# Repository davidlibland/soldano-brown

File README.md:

# Soldano BSIAB
This repo contains schematics and parts lists for a soldano clone based on the Brown Sound in a Box (BSIAB) pedal. It relies on cascading push-pull jfets.

It fits this enclosure: https://www.taydaelectronics.com/hardware/enclosures/matte-white-pedalpcb-125b-bare-drilled-enclosure-type-5-1.html

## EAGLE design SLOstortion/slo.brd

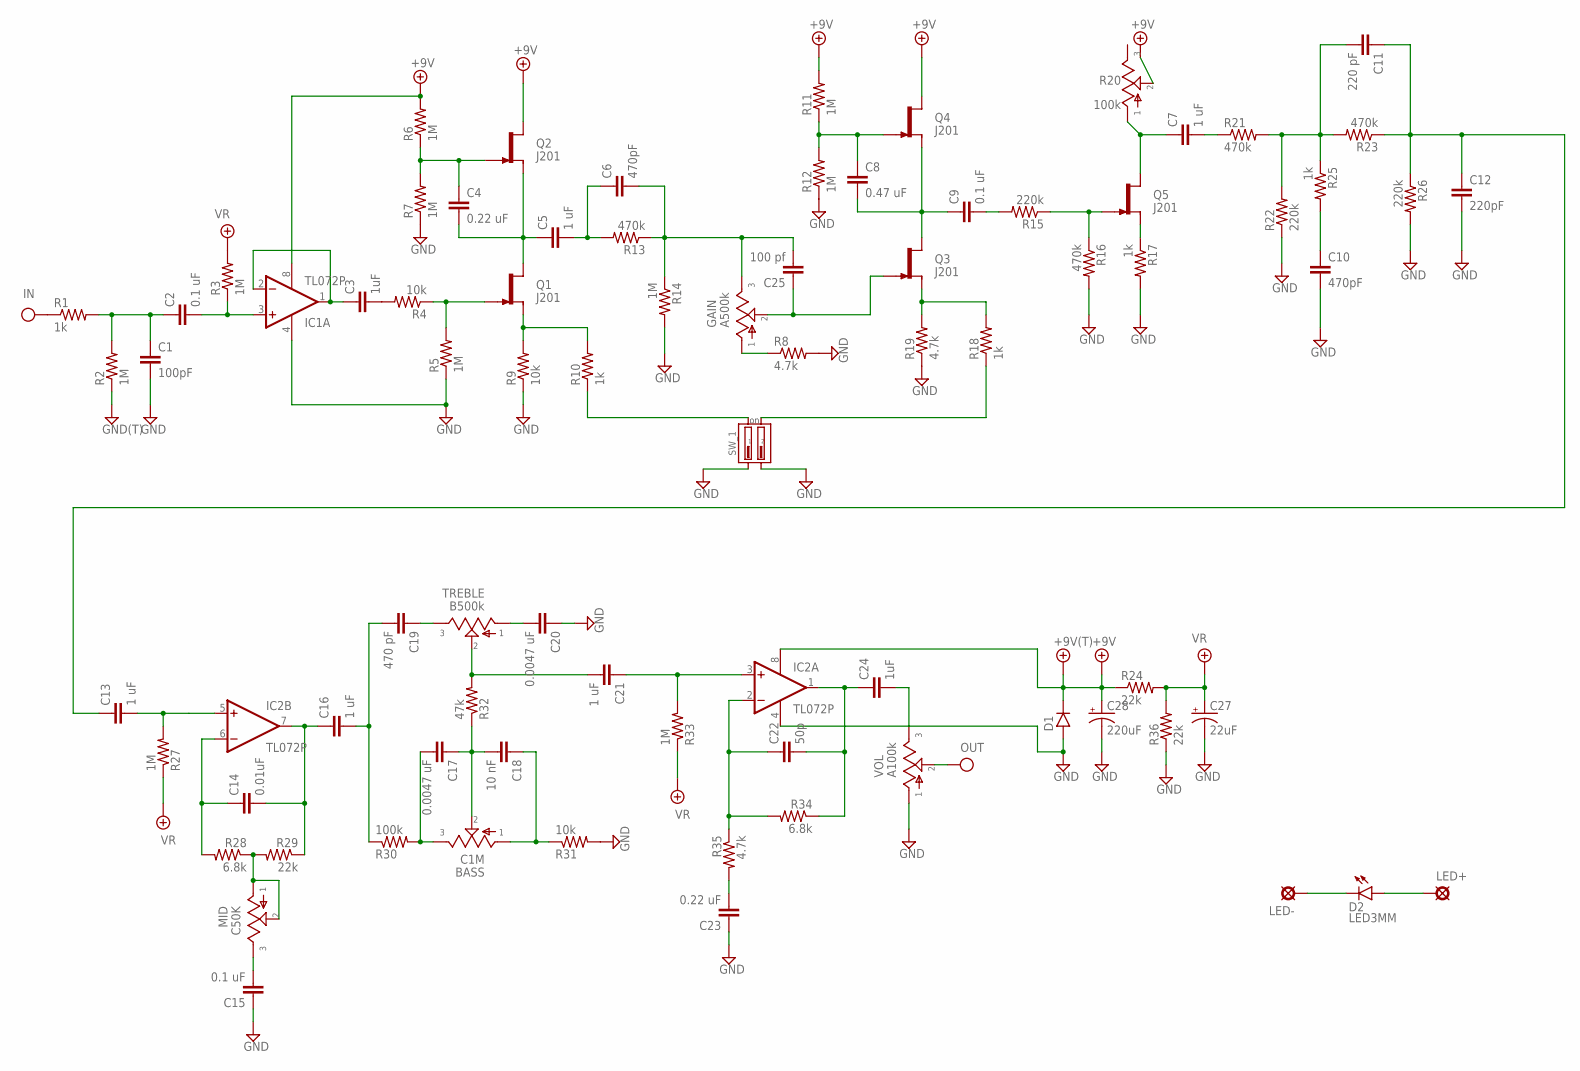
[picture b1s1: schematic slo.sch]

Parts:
+9V: +9V(T); SQUARE
BASS: C1M; 16MM
C1: 100pF; 050X030_050
C2, C9: 0.1 uF; 080X045
C3, C24: 1uF; 080X050
C4, C23: 0.22 uF; 080X045
C5: 1 uF; 070X030
C6: 470pF; 050X030_050
C7, C13, C16, C21: 1 uF; 080X050
C8: 0.47 uF; 080X045
C10: 470pF; 070X030
C11: 220 pF; 075X035_3
C12: 220pF; 075X035_3
C14: 0.01uF; 050X030_050_1
C15: 0.1 uF; 075X040_3
C17, C20: 0.0047 uF; 075X035
C18: 10 nF; 075X035
C19: 470 pF; 075X030
C22: 50p; 050X030_050_1
C25: 100 pf; 050X030_050_1
C27: 22uF; 050_020
C28: 220uF; 063_025
D1: 1N400X.1; DO41-1
D2: LED3MM
GAIN: A500k; 16MM
GND: GND(T); SQUARE
IC1, IC2: TL072P; DIL08
IN: IN(T); SQUARE
LED+: PADO; ROUND
LED-: PAD; SQUARE
MID: C50K; 16MM
OUT: OUT(T); SQUARE
Q1, Q2, Q3, Q4, Q5: J201; TO92-
R1, R10, R17, R18, R25: 1k; R0204/2
R2, R3, R5, R6, R7, R11, R12, R14, R27, R33: 1M; R0204/2
R4, R9, R31: 10k; R0204/2
R8, R19, R35: 4.7k; R0204/2
R13, R16, R21, R23: 470k; R0204/2
R15, R22, R26: 220k; R0204/2
R20: 100k; B25P
R24, R29, R36: 22k; R0204/2
R28, R34: 6.8k; R0204/2
R30: 100k; R0204/2
R32: 47k; R0204/2
SW_1: DIP2; DIP2.B
TREBLE: B500k; 16MM
VOL: A100k; 16MM

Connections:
+9V: +9V.1, C28.+, D1.C, IC1.8 (V+), IC2.8 (V+), Q2.3 (D), Q4.3 (D), R6.2, R11.2, R20.2, R24.1
GND: C1.2, C10.2, C12.2, C15.1, C20.1, C23.1, C27.-, C28.-, D1.A, GND.1, IC1.4 (V-), IC2.4 (V-), R2.1, R5.1, R7.1, R8.2, R9.1, R12.1, R14.2, R16.2, R17.2, R19.1, R22.1, R26.2, R31.2, R36.1, SW_1.P$1 (1), SW_1.P$3 (3), VOL.1
IN: IN.1, R1.1
unnamed: C1.1, C2.1, R1.2, R2.2
unnamed: C2.2, IC1.3 (+IN), R3.1
unnamed: C3.1, IC1.1 (OUT), IC1.2 (-IN)
unnamed: C25.1, GAIN.2, Q3.1 (G)
unnamed: C3.2, R4.2
unnamed: Q1.1 (G), R4.1, R5.2
unnamed: Q1.2 (S), R9.2, R10.2
unnamed: C5.2, C6.1, R13.2
unnamed: Q5.1 (G), R15.1, R16.1
unnamed: C6.2, C25.2, GAIN.3, R13.1, R14.1
unnamed: C10.1, R25.2
unnamed: Q3.2 (S), R18.2, R19.2
unnamed: C4.2, C5.1, Q1.3 (D), Q2.2 (S)
unnamed: GAIN.1, R8.1
unnamed: C8.2, C9.1, Q3.3 (D), Q4.2 (S)
unnamed: C4.1, Q2.1 (G), R6.1, R7.2
unnamed: C8.1, Q4.1 (G), R11.1, R12.2
unnamed: C9.2, R15.2
unnamed: Q5.2 (S), R17.1
unnamed: C7.1, Q5.3 (D), R20.1
unnamed: C7.2, R21.1
unnamed: C14.2, C16.1, IC2.7 (OUT), R29.1
unnamed: MID.1, MID.2, R28.1, R29.2
unnamed: C14.1, IC2.6 (-IN), R28.2
unnamed: C16.2, C19.2, R30.1
unnamed: C15.2, MID.3
unnamed: C11.1, C12.1, C13.1, R23.1, R26.1
unnamed: BASS.3, C17.2, R30.2
unnamed: D2.K (C), LED-.1
unnamed: C13.2, IC2.5 (+IN), R27.2
unnamed: BASS.1, C18.1, R31.1
unnamed: C11.2, R21.2, R22.2, R23.2, R25.1
unnamed: BASS.2, C17.1, C18.2, R32.1
unnamed: C19.1, TREBLE.3
unnamed: C21.2, R32.2, TREBLE.2
unnamed: C20.2, TREBLE.1
unnamed: C21.1, IC2.3 (+IN), R33.2
unnamed: D2.A, LED+.1
unnamed: C22.1, IC2.2 (-IN), R34.2, R35.1
unnamed: C22.2, C24.1, IC2.1 (OUT), R34.1
unnamed: C23.2, R35.2
unnamed: R18.1, SW_1.P$4 (4)
unnamed: C24.2, VOL.3
unnamed: R10.1, SW_1.P$2 (2)
OUT: OUT.1, VOL.2
VR: C27.+, R3.2, R24.2, R27.1, R33.1, R36.2

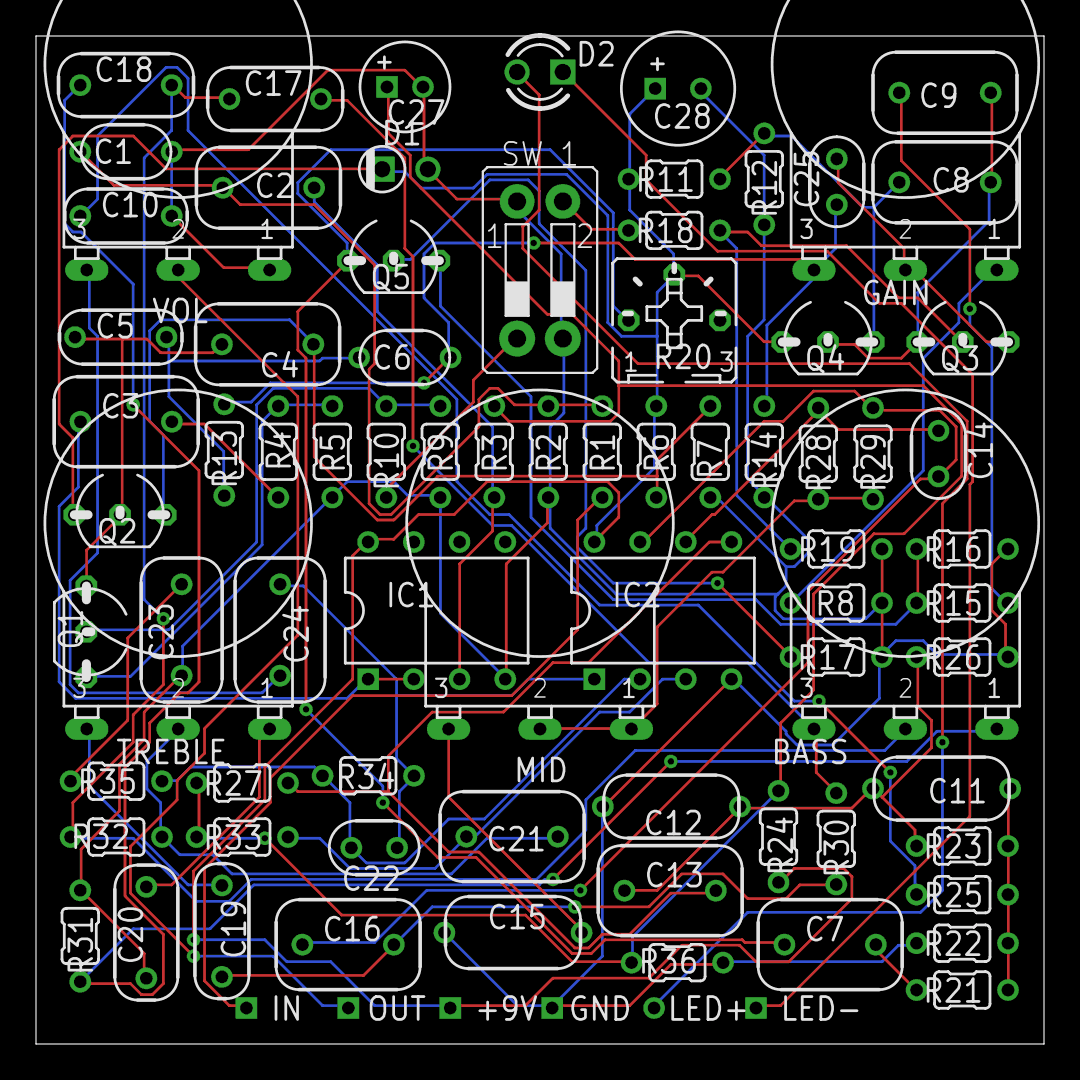
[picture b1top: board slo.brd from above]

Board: 2 copper layers, 56.0 x 56.0 mm, 84 parts (0 on the bottom side), 49 nets.

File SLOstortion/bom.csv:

Qty,Value,Device,Package,Parts,Description,,
1,,1N400X.1,DO41-1,D1,Rectifier Diodes,,
1,+9V(T),+9V(T),SQUARE,+9V1,+9V Voltage Supply,,
2,0.0047 uF,075X0352,075X035,"C17, C20",0.027 - 0.033uF,,
1,0.01uF,050X030_0501,050X030_050_1,C14,120 - 150pF,,
2,0.1 uF,080X0452,080X045,"C2, C9",0.056 - 0.082uF,,
1,0.1 uF,080X0453,075X040_3,C15,0.056 - 0.082uF,,
2,0.22 uF,080X0452,080X045,"C4, C23",0.056 - 0.082uF,,
1,0.47 uF,080X0452,080X045,C8,0.056 - 0.082uF,,
1,1 uF,070X0302,070X030,C5,"0.0001 - .01uF (100 - 10,000pF)",,
4,1 uF,080X0502,080X050,"C7, C13, C16, C21",0.1uF,,
1,10 nF,075X0352,075X035,C18,0.027 - 0.033uF,,
1,100 pf,050X030_0501,050X030_050_1,C25,120 - 150pF,,
1,100k,POTTRIM,B25P,R20,Potentiometers,,
1,100pF,050X030_0502,050X030_050,C1,120 - 150pF,,
2,10k,3MM.2,R0204/2,"R4, R9",3mm Resistors,,
1,1K,3MM.2,R0204/2,R17,3mm Resistors,,
10,1M,3MM.2,R0204/2,"R2, R3, R5, R6, R7, R11, R12, R14, R27, R33",3mm Resistors,,
4,1k,3MM.2,R0204/2,"R1, R10, R18, R25",3mm Resistors,,
2,1uF,080X0502,080X050,"C3, C24",0.1uF,,
1,220 pF,075X0353,075X035_3,C11,0.027 - 0.033uF,,
3,220k,3MM.2,R0204/2,"R15, R22, R26",3mm Resistors,,
1,220pF,075X0353,075X035_3,C12,0.027 - 0.033uF,,
1,220uF,631,063_025,C28,33 - 220uF,,
3,22k,3MM.2,R0204/2,"R24, R29, R36",3mm Resistors,,
1,22uF,50,050_020,C27,0.22 - 100uF,,
1,33k,3MM.2,R0204/2,R30,3mm Resistors,,
3,4.7k,3MM.2,R0204/2,"R8, R19, R35",3mm Resistors,,
1,470 pF,075X0302,075X030,C19,0.015 - 0.022uF,,
4,470k,3MM.2,R0204/2,"R13, R16, R21, R23",3mm Resistors,,
1,470pF,050X030_0502,050X030_050,C6,120 - 150pF,,
2,47k,3MM.2,R0204/2,"R31, R32",3mm Resistors,,
1,50p,050X030_0501,050X030_050_1,C22,120 - 150pF,,
2,6.8k,3MM.2,R0204/2,"R28, R34",3mm Resistors,,
1,A100k,POT,POT,VOL,Potentiometers,,
1,A500k,POT,POT,GAIN,Potentiometers,,
1,B500k,POT,POT,TREBLE,Potentiometers,,
1,C1M,POT,POT,BASS,Potentiometers,,
1,C50K,POT,POT,MID,Potentiometers,,
1,GND(T),GND(T),SQUARE,GND2,Ground,,
1,IN(T),IN(T),SQUARE,IN1,Input,,
5,J201,J201,TO92-,"Q1, Q2, Q3, Q4, Q5",N-channel JFET,,
1,OUT(T),OUT(T),SQUARE,OUT1,Output,,
2,TL072P,TL072P,DIL08,"IC1, IC2",OP AMP,,

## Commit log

2022-04-26 Added schematic
